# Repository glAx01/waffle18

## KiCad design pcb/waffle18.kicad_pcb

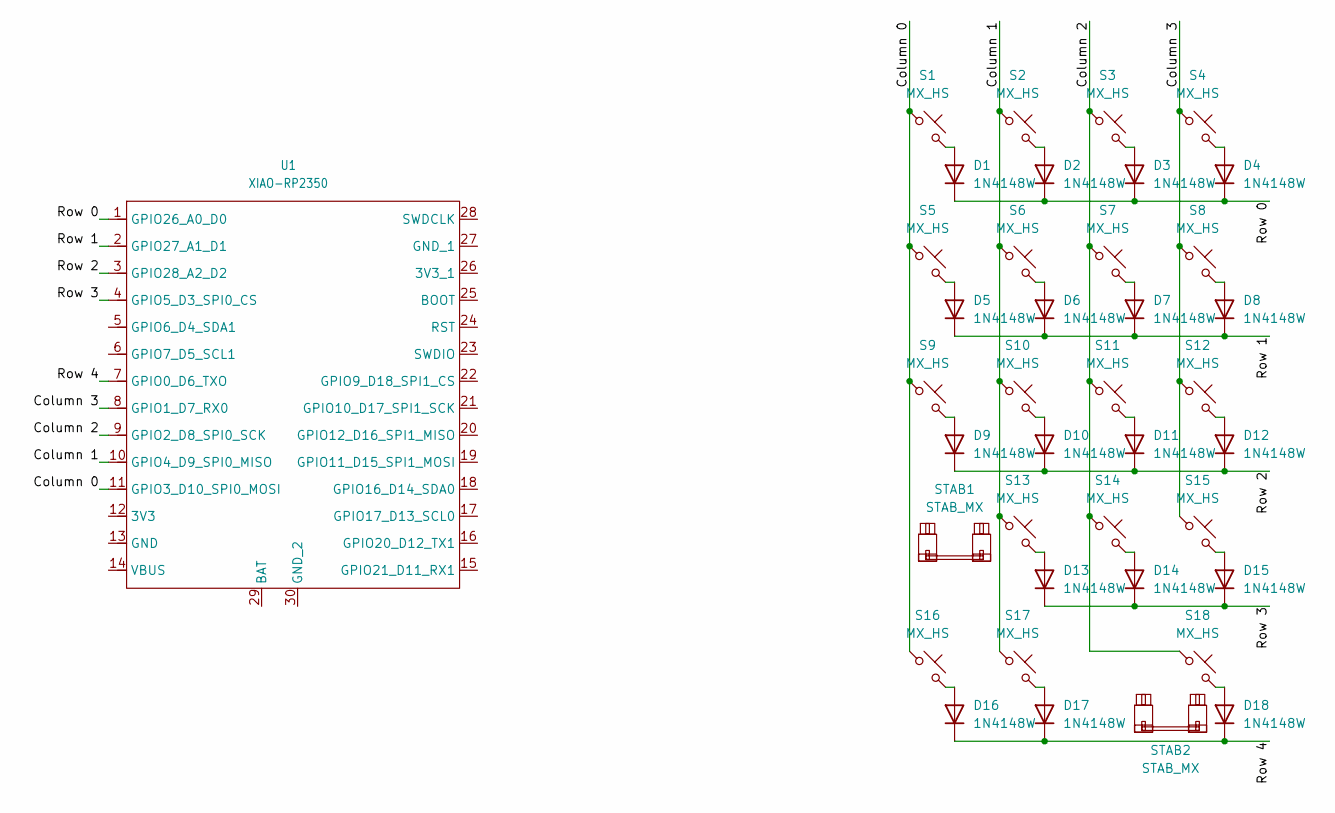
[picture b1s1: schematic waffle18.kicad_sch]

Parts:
D1, D2, D3, D4, D5, D6, D7, D8, D9, D10, D11, D12, D13, D14, D15, D16, D17, D18: 1N4148W; SOD-123
S1, S2, S3, S4, S5, S6, S7, S8, S10, S11, S12, S13, S14, S15, S16, S17: MX_HS; MX_KS-2P02B01-01_1.00u
S9: MX_HS; MX_KS-2P02B01-01_2.00u-V
S18: MX_HS; MX_KS-2P02B01-01_2.00u-H
STAB1, STAB2: STAB_MX; STAB_MX_2.00u
U1: XIAO-RP2350; XIAO_DIP

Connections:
/Column 0: S1.1, S5.1, S9.1, S16.1, U1.11 (GPIO3_D10_SPI0_MOSI)
/Column 1: S2.1, S6.1, S10.1, S13.1, S17.1, U1.10 (GPIO4_D9_SPI0_MISO)
/Column 2: S3.1, S7.1, S11.1, S14.1, S18.1, U1.9 (GPIO2_D8_SPI0_SCK)
/Column 3: S4.1, S8.1, S12.1, S15.1, U1.8 (GPIO1_D7_RX0)
/Row 0: D1.1 (K), D2.1 (K), D3.1 (K), D4.1 (K), U1.1 (GPIO26_A0_D0)
/Row 1: D5.1 (K), D6.1 (K), D7.1 (K), D8.1 (K), U1.2 (GPIO27_A1_D1)
/Row 2: D9.1 (K), D10.1 (K), D11.1 (K), D12.1 (K), U1.3 (GPIO28_A2_D2)
/Row 3: D13.1 (K), D14.1 (K), D15.1 (K), U1.4 (GPIO5_D3_SPI0_CS)
/Row 4: D16.1 (K), D17.1 (K), D18.1 (K), U1.7 (GPIO0_D6_TXO)
unnamed: D1.2 (A), S1.2
unnamed: D2.2 (A), S2.2
unnamed: D3.2 (A), S3.2
unnamed: D4.2 (A), S4.2
unnamed: D5.2 (A), S5.2
unnamed: D6.2 (A), S6.2
unnamed: D7.2 (A), S7.2
unnamed: D8.2 (A), S8.2
unnamed: D9.2 (A), S9.2
unnamed: D10.2 (A), S10.2
unnamed: D11.2 (A), S11.2
unnamed: D12.2 (A), S12.2
unnamed: D13.2 (A), S13.2
unnamed: D14.2 (A), S14.2
unnamed: D15.2 (A), S15.2
unnamed: D16.2 (A), S16.2
unnamed: D17.2 (A), S17.2
unnamed: D18.2 (A), S18.2

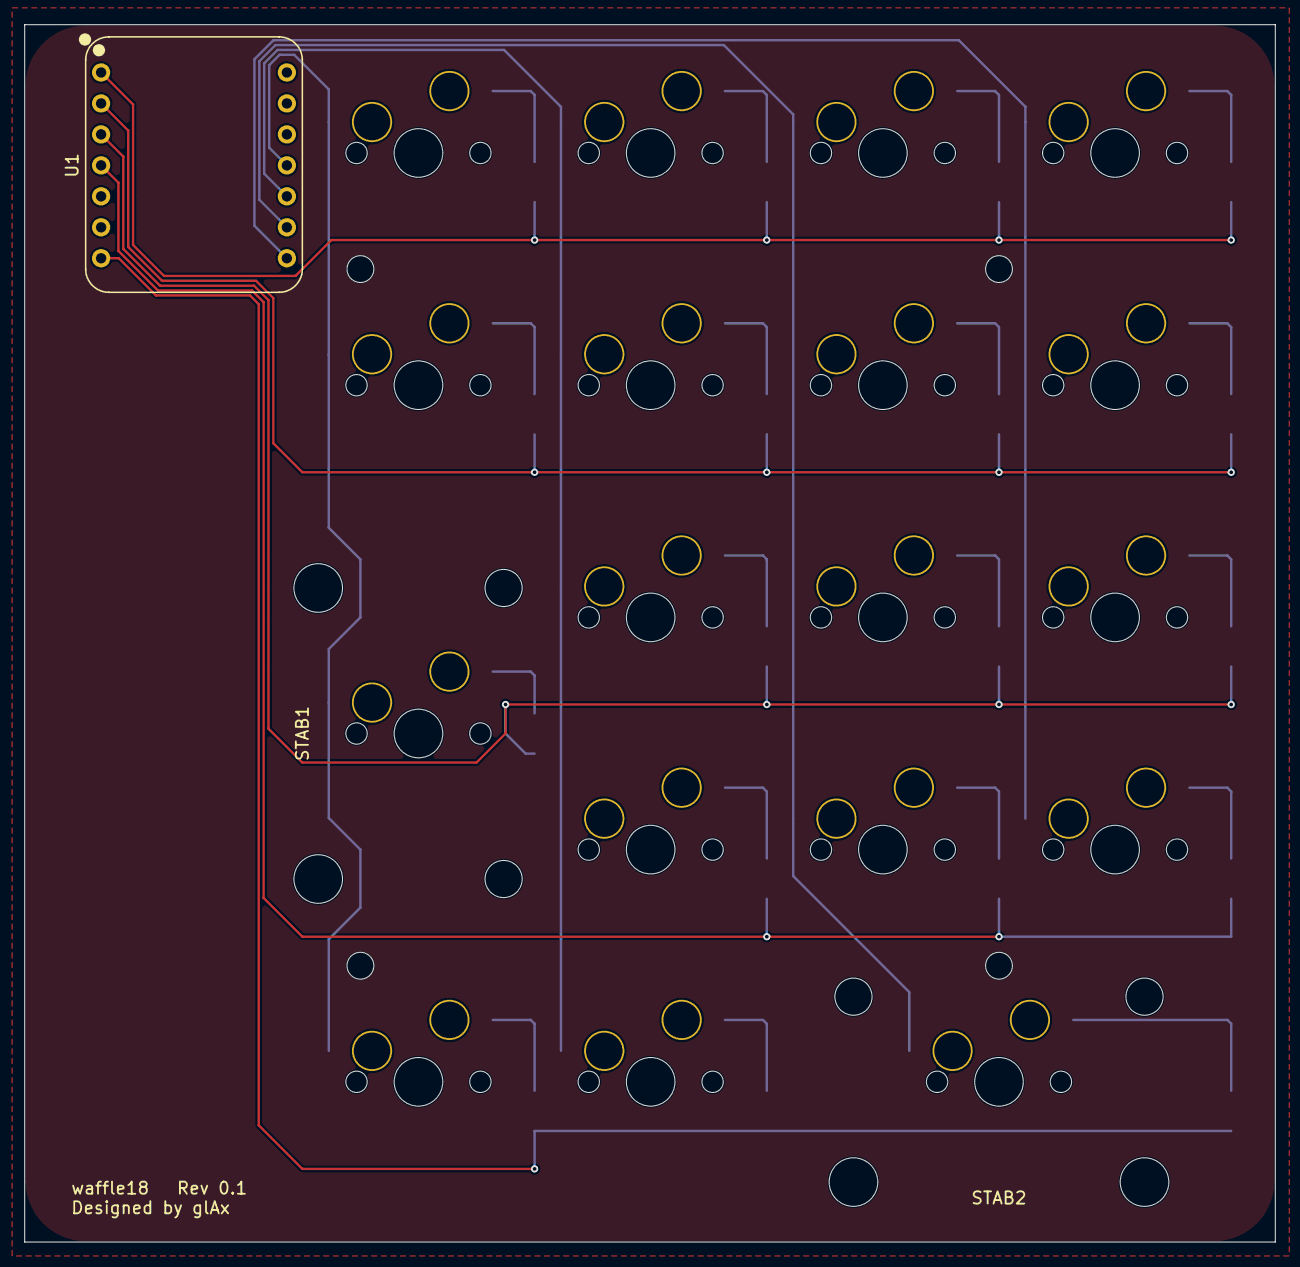
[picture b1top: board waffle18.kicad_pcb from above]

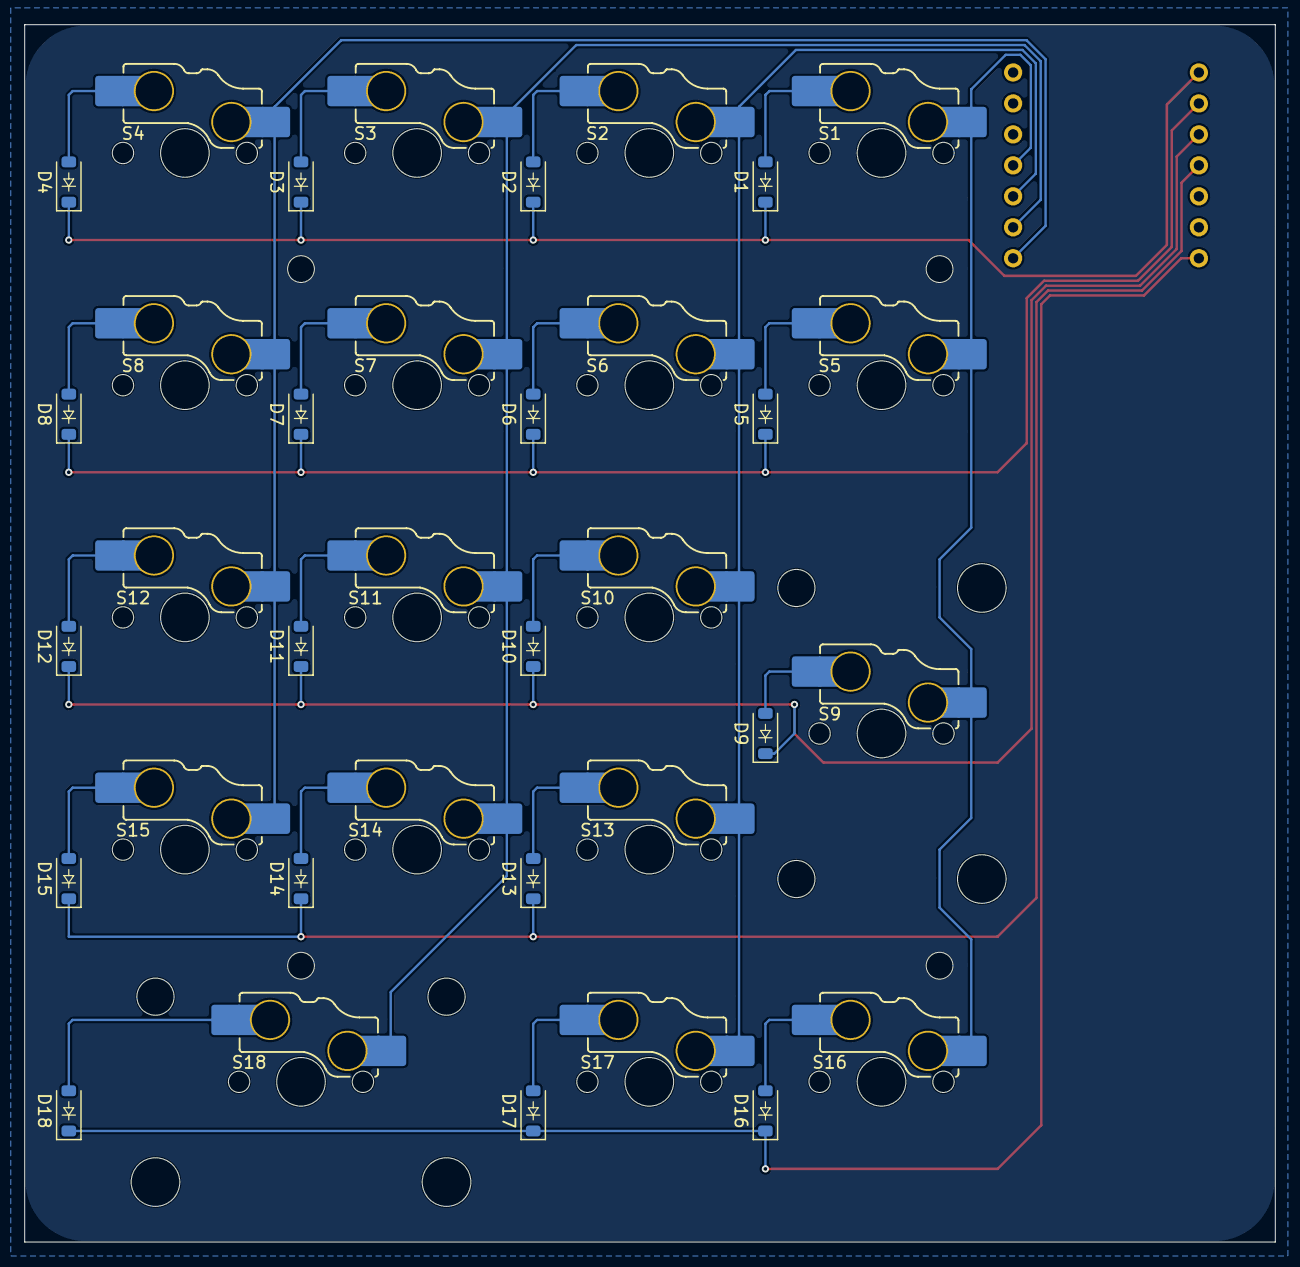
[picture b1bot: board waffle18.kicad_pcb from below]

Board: 2 copper layers, 102.6 x 99.9 mm, 39 parts (36 on the bottom side), 27 nets.

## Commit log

2026-04-24 feat: add symbol, footprints, and 3D models
2026-04-24 feat(footprints): add diode symbol to silkscreen
2026-05-02 feat(3dmodels): add 320020159 sockets to XIAO-RP2350.step
2026-05-02 refactor(footprints): realign 3D model and remove unused holes in XIAO_DIP.kicad_mod
2026-05-05 docs(resources): add licenses and attributions
2026-05-06 docs(resources): update README with Title and Installation
2026-05-06 feat(schematic): add matrix layout
2026-05-06 feat(schematic): connect matrix to XIAO RP2350
2026-05-06 feat(schematic): assign switch and stabilizer footprints
2026-05-08 refactor(schematic): optimize pin assignment for routing
2026-05-08 feat(pcb): place footprints
2026-05-08 feat(pcb): route tracks and place vias
2026-05-09 fix(footprints): increase XIAO_DIP reference size and thickness
2026-05-09 feat(pcb): add edge cuts
2026-05-10 feat(pcb): add mounting holes and filled zone
2026-05-10 chore(pcb): prepare for production

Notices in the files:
parts and their libraries:
MX_stab by ebastler/marbastlib on GitHub, used under CERN-OHL-P-2.0 / Modified field values
XIAO-Add-On by Seeed-Studio/OPL_Kicad_Library on GitHub, used under CC-BY-SA-4.0 / Removed unused holes and solderpaste margin overrides
